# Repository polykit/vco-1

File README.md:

# Polykit VCO-1

This repository contains schematics and PCB layout for a voltage controlled oscillator (VCO). The goal was to keep price and component count low while having a good 1V/oct tracking. The oscillator core is roughly bases on the Jupiter 8 with a simpler approach for the current sink. It either needs a pair of matched 2N3904 transistors or one BC847BS dual transistor. I have very good results with the BC847BS and an accurate tracking over several octaves. On the output it generates a ramp and a pulse signal with 10Vpp amplitude. There is also a CV input for pulse width modulation.

Note: PCB also contains a simple sub-oscillator with output for one and two octaves down

There is also a PCB version with [eight oscillators on it](https://github.com/polykit/vco-8).

# References

https://www.muffwiggler.com/forum/viewtopic.php?t=92595

https://kassu2000.blogspot.com/2015/12/vco-part-1-core.html

https://kassu2000.blogspot.com/2015/10/transistor-matching.html

http://www.synthdiy.com/files/2008/RolandJupiter8-ServiceNotes.pdf

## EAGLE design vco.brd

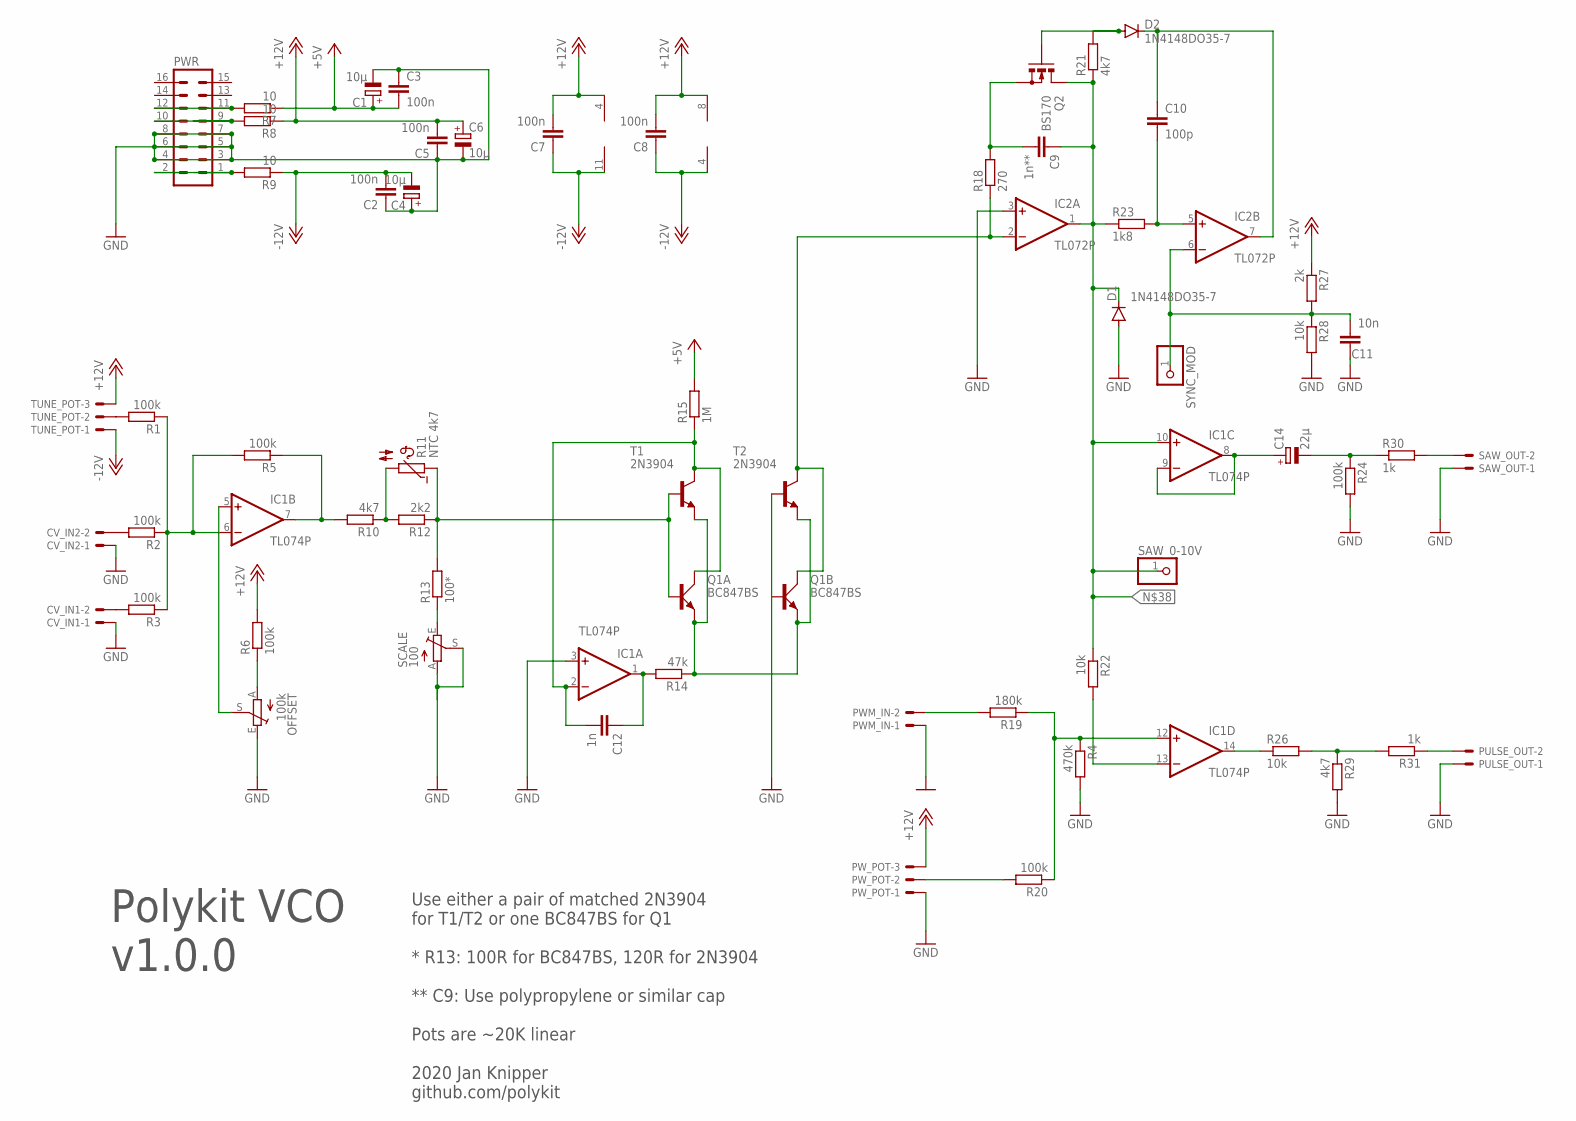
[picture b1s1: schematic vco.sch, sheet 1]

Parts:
C1, C4, C6: 10µ; E2,5-5
C2, C3, C5, C7, C8: 100n; C050-030X075
C9: 1n**; C050-030X075
C10: 100p; C050-030X075
C11: 10n; C050-030X075
C12: 1n; C050-024X044
C14: 22µ; E2,5-5
CV_IN1, CV_IN2: 22-23-2021
D1, D2: 1N4148DO35-7; DO35-7
IC1: TL074P; DIL14
IC2: TL072P; DIL08
OFFSET: 100k; S64YW
PULSE_OUT: 22-23-2021
PWM_IN: 22-23-2021
PWR: ML16
PW_POT: 22-23-2031
Q1: BC847BS; SOT363_PHILIPS
Q2: BS170; SOT54E
R1, R2, R3, R5, R6, R20, R24: 100k; 0207/7
R4: 470k; 0207/7
R7, R8, R9: 10; 0207/7
R10, R21, R29: 4k7; 0207/7
R11: NTC 4k7; P640
R12: 2k2; 0207/7
R13: 100*; 0207/7
R14: 47k; 0207/7
R15: 1M; 0207/7
R18: 270; 0207/7
R19: 180k; 0207/7
R22, R26, R28: 10k; 0207/7
R23: 1k8; 0207/7
R27: 2k; 0207/7
R30, R31: 1k; 0207/7
SAW_0-10V: PINHD-1X1; 1X01
SAW_OUT: 22-23-2021
SCALE: 100; S64YW
SYNC_MOD: PINHD-1X1; 1X01
T1, T2: 2N3904; TO92
TUNE_POT: 22-23-2031

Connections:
+5V: C1.+, C3.2, R7.1, R15.2
+12V: C5.2, C6.+, C7.2, C8.2, IC1.4 (V+), IC2.8 (V+), PW_POT.3, R6.2, R8.1, R27.1, TUNE_POT.3; also elsewhere on the board
-12V: C2.2, C4.-, C7.1, C8.1, IC1.11 (V-), IC2.4 (V-), R9.1, TUNE_POT.1
GND: C1.-, C2.1, C3.1, C4.+, C5.1, C6.-, C11.1, CV_IN1.1, CV_IN2.1, D1.A, IC1.3 (+IN), IC2.3 (+IN), OFFSET.E, PULSE_OUT.1, PWM_IN.1, PWR.3, PWR.4, PWR.5, PWR.6, PWR.7, PWR.8, PW_POT.1, Q1.5 (B), R4.2, R24.2, R28.2, R29.2, SAW_OUT.1, SCALE.A, SCALE.S, T2.2 (B); also elsewhere on the board
unnamed: PWR.1, PWR.2, R9.2
unnamed: Q1.1 (E), Q1.4 (E), R14.1, T1.3 (E), T2.3 (E)
unnamed: C12.2, IC1.2 (-IN), Q1.6 (C), R15.1, T1.1 (C)
unnamed: PWR.9, PWR.10, R8.2
unnamed: Q1.2 (B), R11.1, R12.1, R13.2, T1.2 (B)
unnamed: C14.-, R24.1, R30.1
unnamed: PULSE_OUT.2, R31.1
unnamed: IC1.7 (OUT), R5.1, R10.2
unnamed: R1.2, TUNE_POT.2
unnamed: C10.1, D2.C, IC2.7 (OUT)
unnamed: OFFSET.A, R6.1
unnamed: CV_IN2.2, R2.2
unnamed: CV_IN1.2, R3.2
unnamed: C14.+, IC1.8 (OUT), IC1.9 (-IN)
unnamed: R30.2, SAW_OUT.2
unnamed: IC1.13 (-IN), R22.2
unnamed: IC1.14 (OUT), R26.1
unnamed: R26.2, R29.1, R31.2
unnamed: IC1.12 (+IN), R4.1, R19.1, R20.1
unnamed: PWM_IN.2, R19.2
unnamed: PW_POT.2, R20.2
unnamed: IC1.5 (+IN), OFFSET.S
unnamed: R10.1, R11.2, R12.2
unnamed: C10.2, IC2.5 (+IN), R23.2
unnamed: PWR.11, PWR.12, R7.2
unnamed: C12.1, IC1.1 (OUT), R14.2
unnamed: C9.2, Q2.S, R18.2
unnamed: D2.A, Q2.G, R21.2
unnamed 41: C9.1, D1.C, IC1.10 (+IN), IC2.1 (OUT), Q2.D, R21.1, R22.1, R23.1, SAW_0-10V.1; also elsewhere on the board
unnamed: C11.2, IC2.6 (-IN), R27.2, R28.1, SYNC_MOD.1
unnamed: IC2.2 (-IN), Q1.3 (C), R18.1, T2.1 (C)
unnamed: R13.1, SCALE.E
unnamed: IC1.6 (-IN), R1.1, R2.1, R3.1, R5.2

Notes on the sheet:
Use either a pair of matched 2N3904 for T1/T2 or one BC847BS for Q1 * R13: 100R for BC847BS, 120R for 2N3904 ** C9: Use polypropylene or similar cap Pots are ~20K linear 2020 Jan Knipper github.com/polykit
Polykit VCO v1.0.0

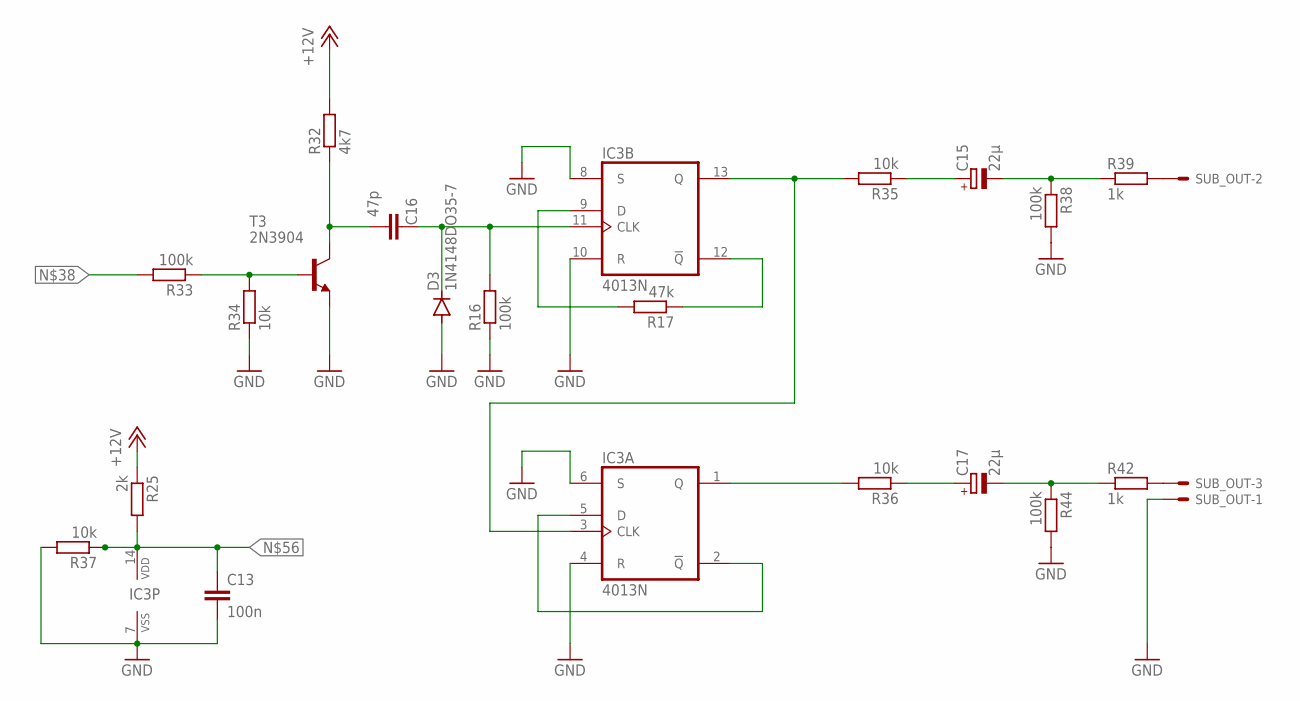
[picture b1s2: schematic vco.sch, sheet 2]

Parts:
C13: 100n; C050-030X075
C15, C17: 22µ; E2,5-5
C16: 47p; C050-030X075
D3: 1N4148DO35-7; DO35-7
IC3: 4013N; DIL14
R16, R33, R38, R44: 100k; 0207/7
R17: 47k; 0207/7
R25: 2k; 0207/7
R32: 4k7; 0207/7
R34, R35, R36, R37: 10k; 0207/7
R39, R42: 1k; 0207/7
SUB_OUT: 22-23-2031
T3: 2N3904; TO92

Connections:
+12V: R25.1, R32.2; also elsewhere on the board
GND: C13.2, D3.A, IC3.4 (R), IC3.6 (S), IC3.7 (VSS), IC3.8 (S), IC3.10 (R), R16.1, R34.1, R37.2, R38.2, R44.2, SUB_OUT.1, T3.3 (E); also elsewhere on the board
unnamed: R42.2, SUB_OUT.3
unnamed: R33.1, R34.2, T3.2 (B)
unnamed: C16.1, D3.C, IC3.11 (CLK), R16.2
unnamed: IC3.9 (D), R17.2
unnamed: IC3.12 (!Q), R17.1
unnamed: C16.2, R32.1, T3.1 (C)
unnamed: C15.+, R35.1
unnamed: C15.-, R38.1, R39.1
unnamed 41: R33.2; also elsewhere on the board
unnamed: IC3.2 (!Q), IC3.5 (D)
unnamed: IC3.3 (CLK), IC3.13 (Q), R35.2
unnamed: IC3.1 (Q), R36.2
unnamed: C17.+, R36.1
unnamed: R39.2, SUB_OUT.2
unnamed: C17.-, R42.1, R44.1
unnamed: C13.1, IC3.14 (VDD), R25.2, R37.1

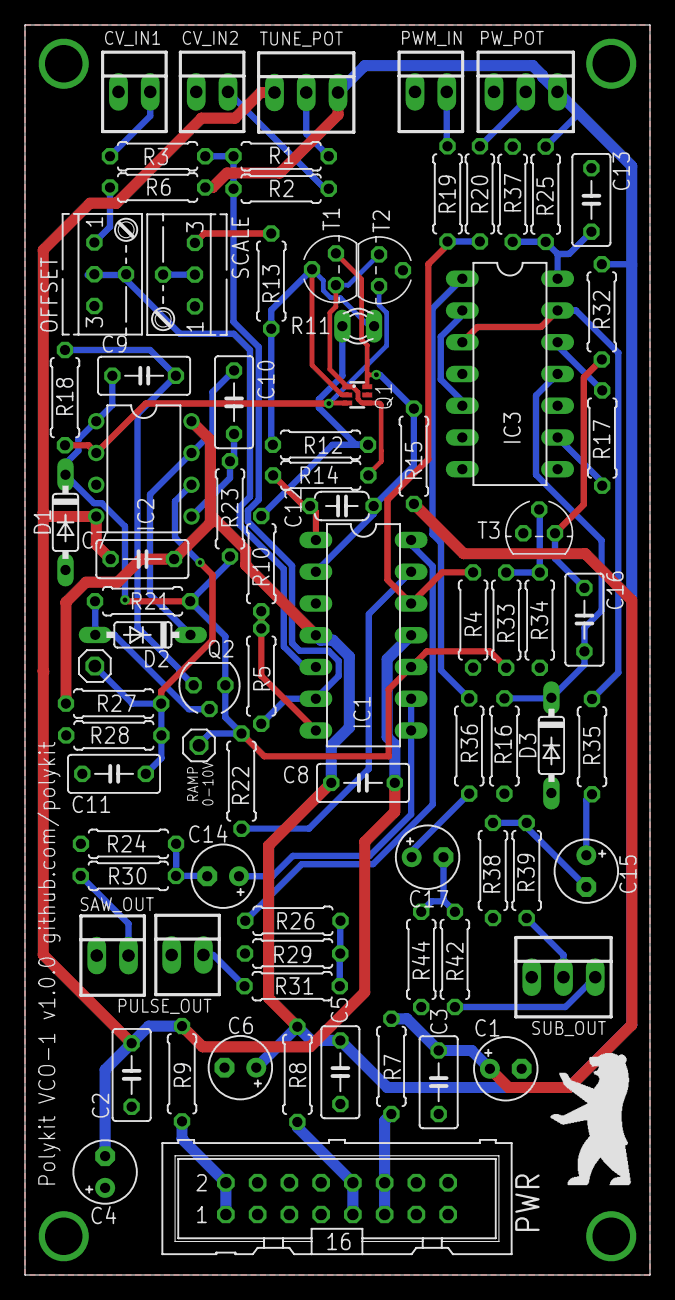
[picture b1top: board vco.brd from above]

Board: 2 copper layers, 50.0 x 100.0 mm, 82 parts (0 on the bottom side), 52 nets.

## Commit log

2021-01-22 Initial import
